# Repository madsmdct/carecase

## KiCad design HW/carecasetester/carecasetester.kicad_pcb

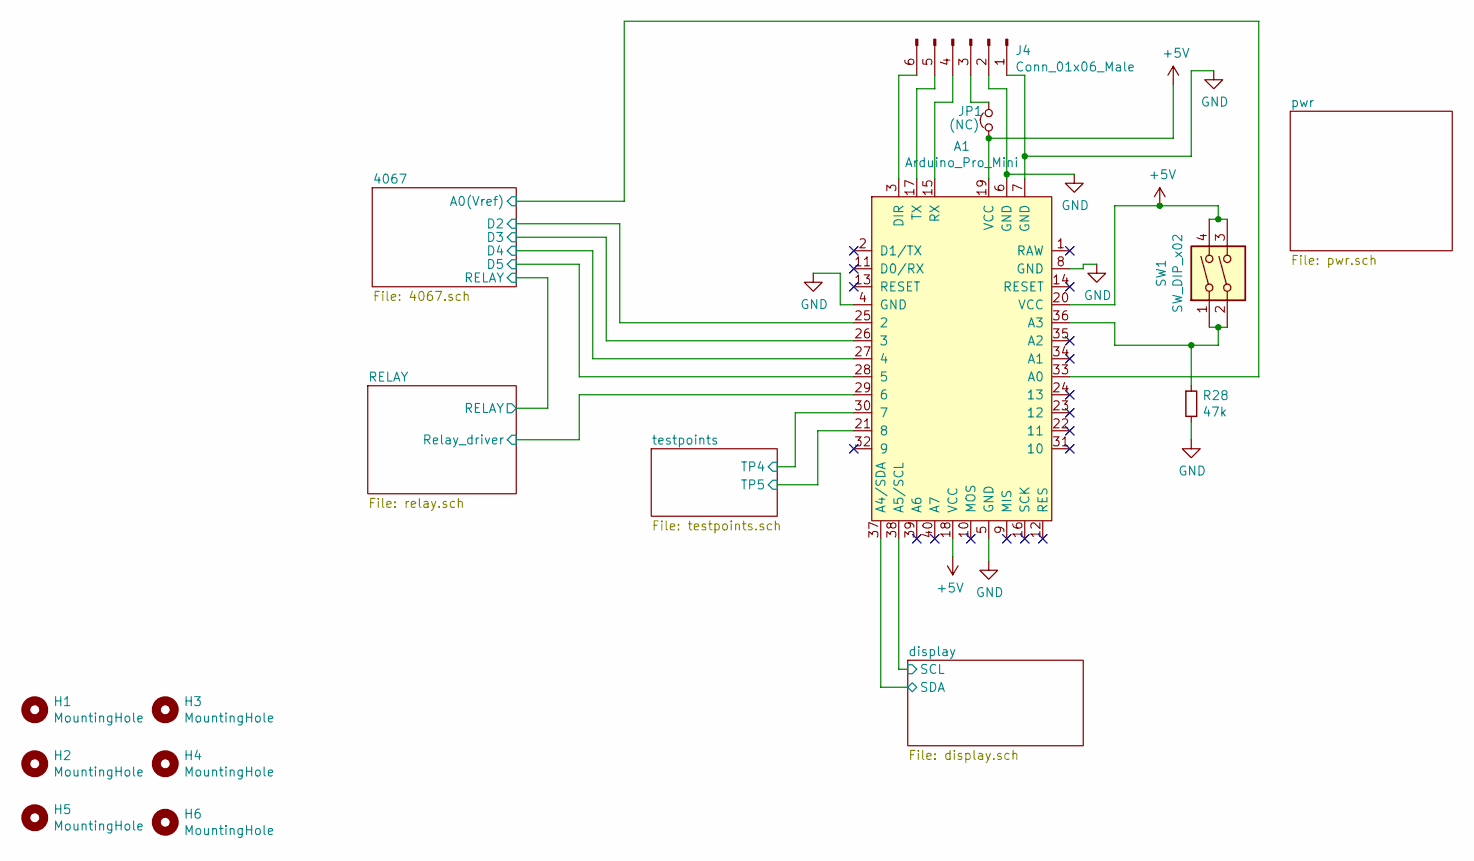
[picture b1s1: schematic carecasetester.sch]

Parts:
A1: Arduino_Pro_Mini; Arduino_Pro_Micro
H1, H2, H3, H4, H5, H6: MountingHole; MountingHole_3.2mm_M3_ISO14580_Pad
J4: Conn_01x06_Male; PinHeader_1x06_P2.54mm_Horizontal
JP1: (NC); Jumper_P2.54_Vertical_THT
R28: 47k; R_0603_1608Metric_Pad1.05x0.95mm_HandSolder
SW1: SW_DIP_x02; SW_TH_Tactile_Omron_B3F-10xx

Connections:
/4067/A0(Vref): A1.33 (A0); also elsewhere on the board
/4067/D2: A1.25 (2); also elsewhere on the board
/4067/D3: A1.26 (3); also elsewhere on the board
/4067/D4: A1.27 (4); also elsewhere on the board
/4067/D5: A1.28 (5); also elsewhere on the board
/RELAY/Relay_driver1: A1.29 (6); also elsewhere on the board
/RELAY/Relay_driver2: A1.32 (9); also elsewhere on the board
/display/SCL: A1.38 (A5/SCL); also elsewhere on the board
/display/SDA: A1.37 (A4/SDA); also elsewhere on the board
/testpoints/TP4: A1.30 (7); also elsewhere on the board
/testpoints/TP5: A1.21 (8); also elsewhere on the board
/testpoints/TP25: A1.24 (13); also elsewhere on the board
GND: A1.4 (GND), A1.5 (GND), A1.6 (GND), A1.7 (GND), A1.8 (GND), J4.1, J4.2, R28.2; also elsewhere on the board
unnamed: A1.3 (DIR), J4.6
unnamed: A1.15 (RX), J4.4
unnamed: A1.17 (TX), J4.5
unnamed: A1.36 (A3), R28.1, SW1.1, SW1.2
unnamed: J4.3, JP1.2

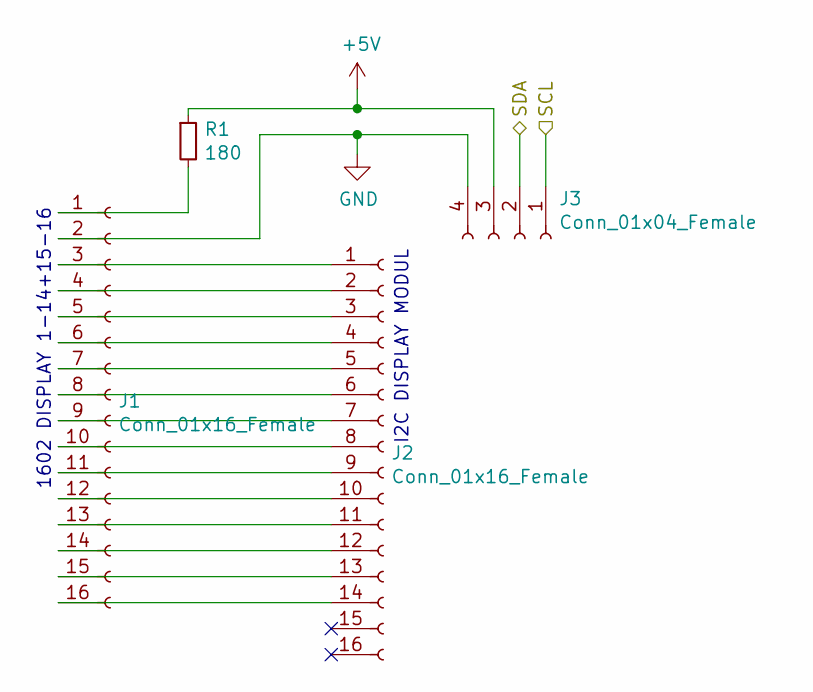
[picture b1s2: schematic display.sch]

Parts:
J1, J2: Conn_01x16_Female; PinSocket_1x16_P2.54mm_Vertical
J3: Conn_01x04_Female; PinSocket_1x04_P2.54mm_Vertical
R1: 180; R_0603_1608Metric_Pad1.05x0.95mm_HandSolder

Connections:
/display/SCL: J3.1; also elsewhere on the board
/display/SDA: J3.2; also elsewhere on the board
GND: J1.2, J3.4; also elsewhere on the board
unnamed: J1.1, R1.2
unnamed: J1.3, J2.1
unnamed: J1.4, J2.2
unnamed: J1.5, J2.3
unnamed: J1.6, J2.4
unnamed: J1.7, J2.5
unnamed: J1.8, J2.6
unnamed: J1.9, J2.7
unnamed: J1.10, J2.8
unnamed: J1.11, J2.9
unnamed: J1.12, J2.10
unnamed: J1.13, J2.11
unnamed: J1.14, J2.12
unnamed: J1.15, J2.13
unnamed: J1.16, J2.14

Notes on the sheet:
I2C DISPLAY MODUL
1602 DISPLAY 1-14+15-16

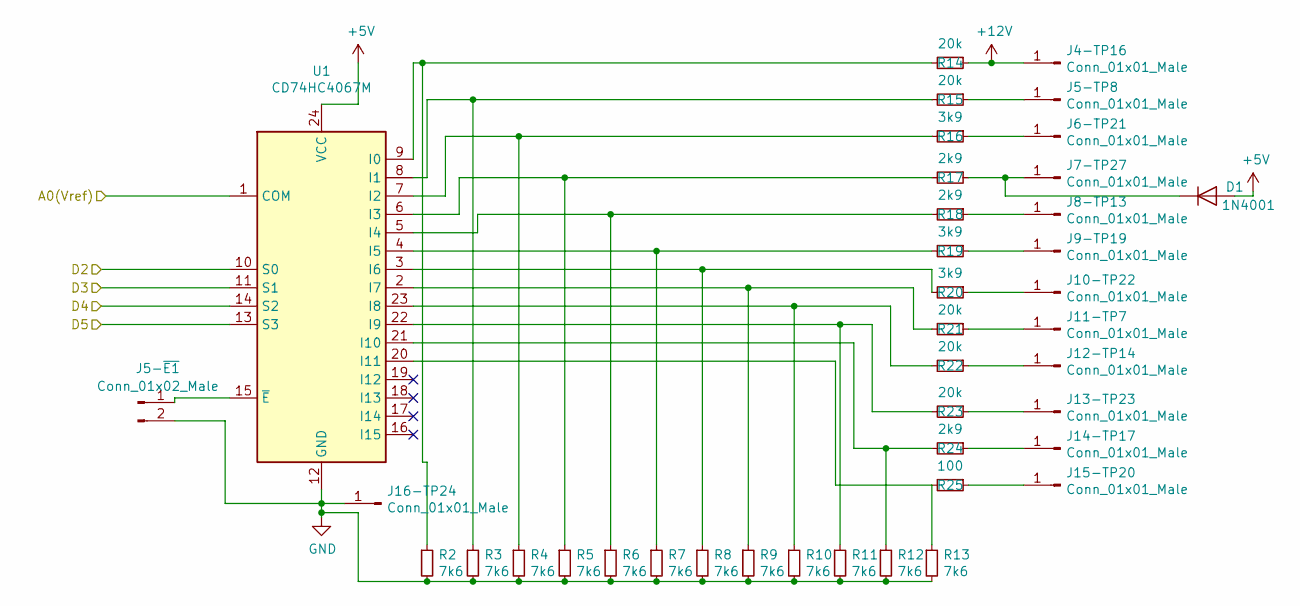
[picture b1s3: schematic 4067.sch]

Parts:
D1: 1N4001; D_DO-41_SOD81_P10.16mm_Horizontal
J4-TP16, J5-TP8, J6-TP21, J7-TP27, J8-TP13, J9-TP19, J10-TP22, J11-TP7, J12-TP14, J13-TP23, J14-TP17, J15-TP20, J16-TP24: Conn_01x01_Male; P50-E-120-G(Pogo)_0.7mmHole_1.5mmPad
J5-~E1: Conn_01x02_Male; PinHeader_1x02_P2.54mm_Horizontal
R2, R3, R4, R5, R6, R7, R8, R9, R10, R11, R12, R13: 7k6
R14, R15, R21, R22, R23: 20k
R16, R19, R20: 3k9
R17, R18, R24: 2k9
R25: 100
U1: CD74HC4067M; SOIC-24W_7.5x15.4mm_P1.27mm

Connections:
/4067/D2: U1.10 (S0); also elsewhere on the board
/4067/D3: U1.11 (S1); also elsewhere on the board
/4067/D4: U1.14 (S2); also elsewhere on the board
/4067/D5: U1.13 (S3); also elsewhere on the board
/4067/RELAY12V: J4-TP16.1, R14.1; also elsewhere on the board
GND: J5-~E1.2, J16-TP24.1, R2.2, R3.2, R4.2, R5.2, R6.2, R7.2, R8.2, R9.2, R10.2, R11.2, R12.2, R13.2, U1.12 (GND); also elsewhere on the board
unnamed: D1.1 (K), J7-TP27.1, R17.1
unnamed: J5-TP8.1, R15.1
unnamed: J5-~E1.1, U1.15 (~E)
unnamed: J6-TP21.1, R16.1
unnamed: J8-TP13.1, R18.1
unnamed: J9-TP19.1, R19.1
unnamed: J10-TP22.1, R20.1
unnamed: J11-TP7.1, R21.1
unnamed: J12-TP14.1, R22.1
unnamed: J13-TP23.1, R23.1
unnamed: J14-TP17.1, R24.1
unnamed: J15-TP20.1, R25.1
unnamed: R10.1, R22.2, U1.23 (I8)
unnamed: R11.1, R23.2, U1.22 (I9)
unnamed: R12.1, R24.2, U1.21 (I10)
unnamed: R13.1, R25.2, U1.20 (I11)
unnamed: R2.1, R14.2, U1.9 (I0)
unnamed: R3.1, R15.2, U1.8 (I1)
unnamed: R4.1, R16.2, U1.7 (I2)
unnamed: R5.1, R17.2, U1.6 (I3)
unnamed: R6.1, R18.2, U1.5 (I4)
unnamed: R7.1, R19.2, U1.4 (I5)
unnamed: R8.1, R20.2, U1.3 (I6)
unnamed: R9.1, R21.2, U1.2 (I7)
unnamed 74: U1.1 (COM); also elsewhere on the board

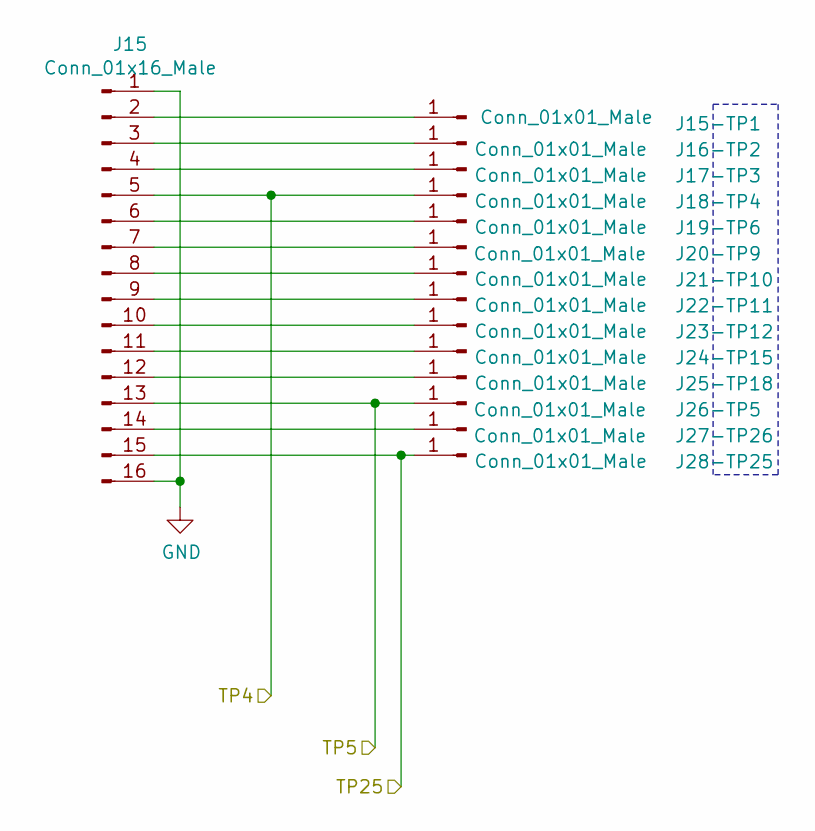
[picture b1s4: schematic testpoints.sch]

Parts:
J15: Conn_01x16_Male; PinHeader_1x16_P2.54mm_Horizontal
J15-TP1, J16-TP2, J17-TP3, J18-TP4, J19-TP6, J20-TP9, J21-TP10, J22-TP11, J23-TP12, J24-TP15, J25-TP18, J26-TP5, J27-TP26, J28-TP25: Conn_01x01_Male; P50-E-120-G(Pogo)_0.7mmHole_1.5mmPad

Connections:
/testpoints/TP4: J15.5, J18-TP4.1; also elsewhere on the board
/testpoints/TP5: J15.13, J26-TP5.1; also elsewhere on the board
/testpoints/TP25: J15.15, J28-TP25.1; also elsewhere on the board
GND: J15.1, J15.16; also elsewhere on the board
unnamed: J15.2, J15-TP1.1
unnamed: J15.3, J16-TP2.1
unnamed: J15.4, J17-TP3.1
unnamed: J15.6, J19-TP6.1
unnamed: J15.7, J20-TP9.1
unnamed: J15.8, J21-TP10.1
unnamed: J15.9, J22-TP11.1
unnamed: J15.10, J23-TP12.1
unnamed: J15.11, J24-TP15.1
unnamed: J15.12, J25-TP18.1
unnamed: J15.14, J27-TP26.1

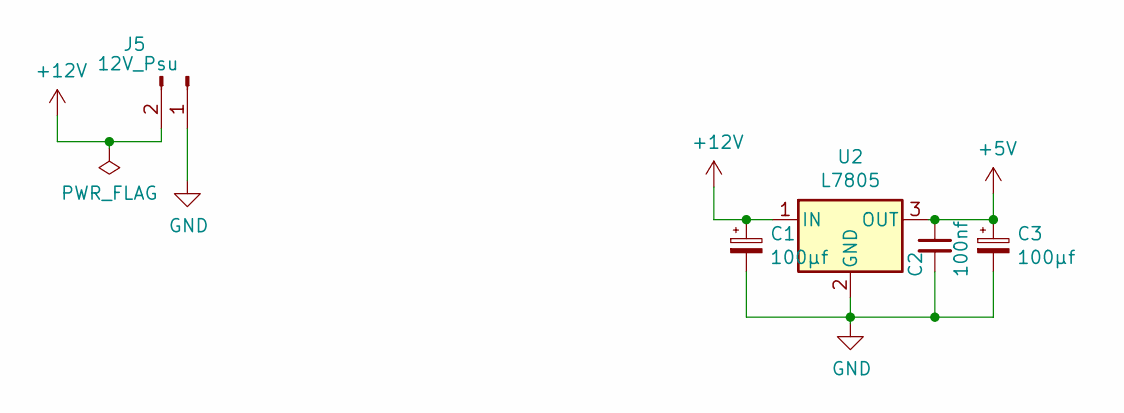
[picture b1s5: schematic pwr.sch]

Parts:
C1, C3: 100µf; CP_Elec_6.3x5.4
C2: 100nf; C_0603_1608Metric_Pad1.05x0.95mm_HandSolder
J5: 12V_Psu; Friwo_Texas_2-pin_Plug(1321609)
U2: L7805; TO-220-3_Horizontal_TabDown

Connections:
+12V: C1.1, J5.2, U2.1 (IN); also elsewhere on the board
GND: C1.2, C2.2, C3.2, J5.1, U2.2 (GND); also elsewhere on the board

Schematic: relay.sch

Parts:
Q1: BC847W; SOT-323_SC-70

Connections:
GND: Q1.2 (E); also elsewhere on the board
unnamed 20: Q1.3 (C); also elsewhere on the board
unnamed 60: Q1.1 (B); also elsewhere on the board

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
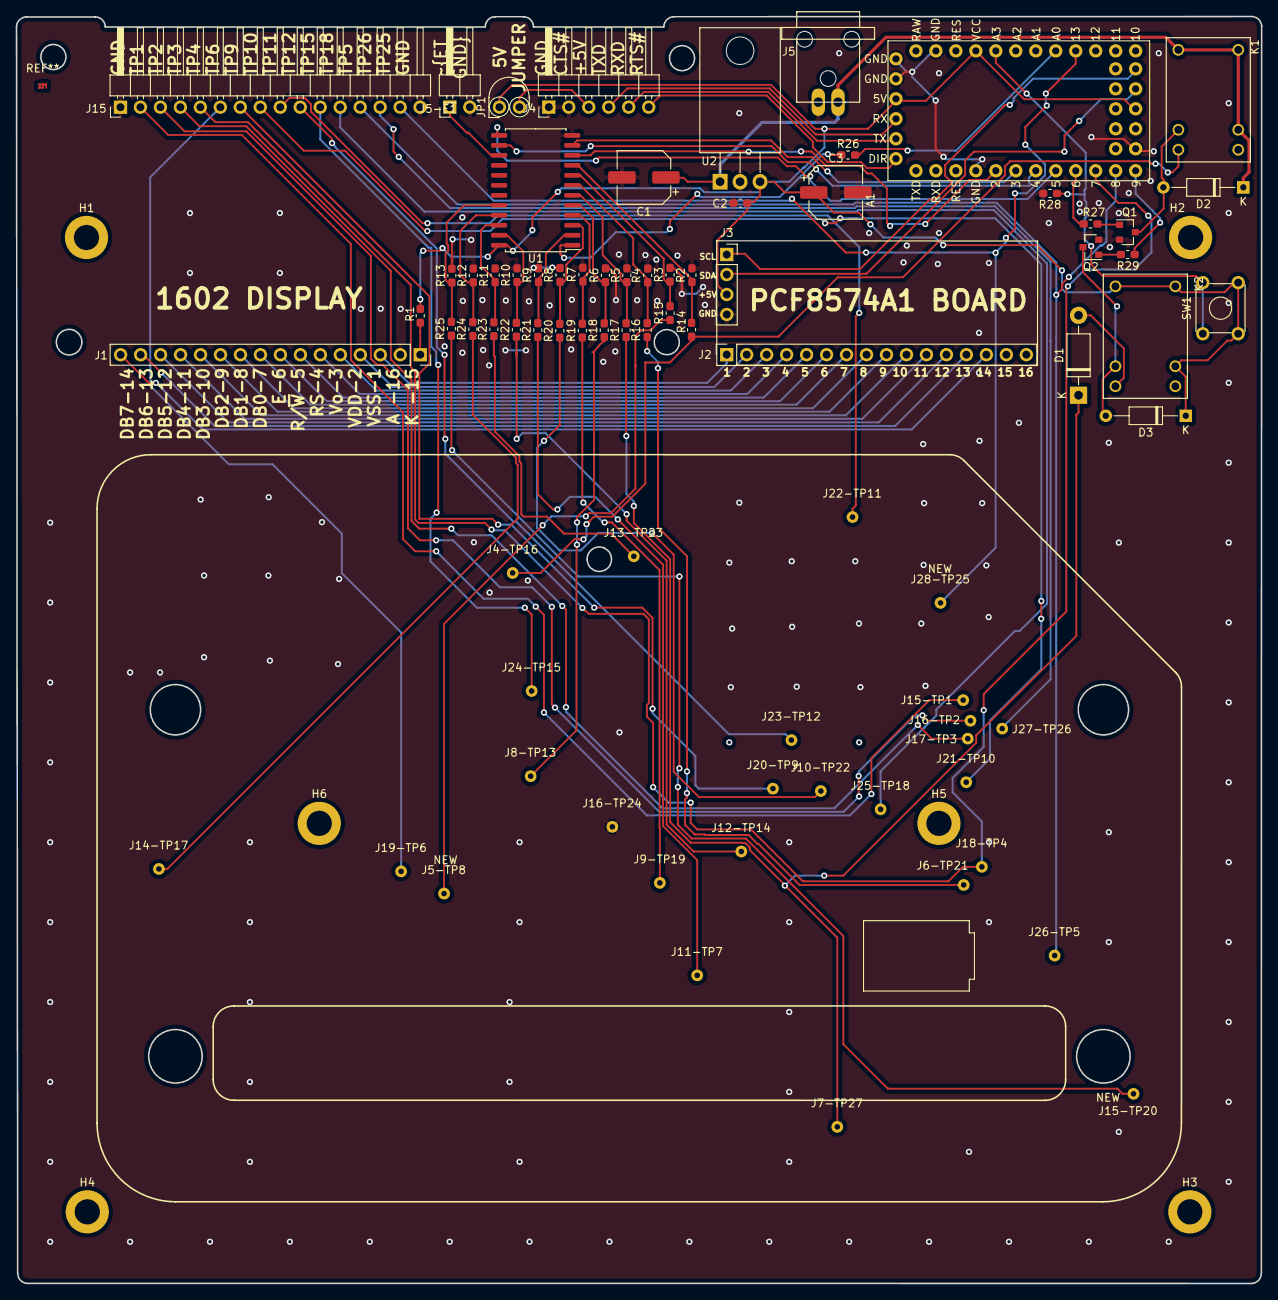
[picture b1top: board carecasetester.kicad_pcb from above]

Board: 2 copper layers, 158.3 x 161.1 mm, 84 parts (0 on the bottom side), 77 nets.

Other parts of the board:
D2, D3: 1N4148W; D_DO-35_SOD27_P10.16mm_Horizontal
K1, K2: AZ952
Q2: BC847W; SOT-23
R26: 100k; R_0603_1608Metric_Pad1.05x0.95mm_HandSolder
R27, R29: 4k7; R_0603_1608Metric_Pad1.05x0.95mm_HandSolder

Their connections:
+12V: D2.1, K1.2, K1.6, K1.7; also elsewhere on the board
/4067/A0(Vref): R26.2; also elsewhere on the board
/4067/RELAY12V: K1.12; also elsewhere on the board
/RELAY/Relay_driver1: R27.2; also elsewhere on the board
/RELAY/Relay_driver2: R29.2; also elsewhere on the board
GND: Q2.2; also elsewhere on the board
unnamed 20: D2.2, K1.11; also elsewhere on the board
unnamed: D3.2, K2.11, Q2.3
unnamed 60: R27.1; also elsewhere on the board
unnamed: Q2.1, R29.1
unnamed 74: R26.1; also elsewhere on the board

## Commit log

2020-02-03 Projekt start I2C display virker
2020-02-03 alle fejl skrevet på mangler verdier på if-er
2020-02-06 HW Schematics done og pcb begun
2020-02-20 cc-tester v0.1 gerber filser genereret og 1. print bestilles
2020-02-20 Complete with gerber V0.1
2020-04-02 missing schematic. (went poof)
2020-04-02 Main sheet saved still need to make relay sheet again
2020-04-02 Relay sheet filled and all pins matched.
    starting changes made to pcb to fit schematic to the new pcb
2020-04-02 First try to fit schematic to pcb (not imported footprints to pcb yet)
    Schematic: All known components has gotten an updated footprint
2020-04-02 PCB and Schematic are synced and gerbers can be made
2020-04-02 Fiksed silk front and back
2020-04-02 Software updated and some issues are fixed
2020-04-03 Gerbers and drillfiles made and ready to order
    edge cuts file renamed to GML instaid of GM1
2020-04-06 V0.22 gerbers
    2nd relay added and all should now be ready to order
2020-04-06 relay schematic didnt commit last commit
2020-04-06 sowtware continnued
2020-04-08 Software almost done..
    waiting for new pcb to adjust the values and set 5v relay port.
2020-04-21 sw opdateret til nyt print
2020-04-28 Kode virker og pcb virker
2020-04-28 Pogo shield finished Rev 0.XX
2020-04-28 int ErrorCode = 0; included and made to work print ok works
2020-04-28 sw almost ready
    still missing serial monitor values for adc read
2020-04-28 Fixed spelling, syntax and EVER-ness.
2020-04-28 10x messure made
2020-05-15 working speaker outputs set with pull down (internal arduino)
2020-08-03 CC tester : tp25 added tp8 moved tp20 moved
2020-08-03 SW notes begun
    HW new edit begun
2020-08-07 pcb updated for new rev. ready to plot gerbers
    footprints saved for later use
    software fixed PCF8574A1 now works with new setup and with in house displays
2020-08-07 dfgdfg
2020-08-17 gerbers and drill files made
2020-08-17 gerbers made last ref before end
2020-08-17 gerber zip added
